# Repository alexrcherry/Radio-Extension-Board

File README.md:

# Radio-Extension-Board
KiCad PCB design files 

## Purpose
The purpose of this board is to transmit data to the ground station and also to determine altitude. Recovery on liquid rockets does not have a good track record so it is good to get max altitude data back to the ground without requiring the recovery to work. The radio chip used for this board also has the ability to do ranging. With multiple ground stations spaced apart, a primitive form of GPS can be used to determine the position and altitude of the rocket. This may be the primary form of altitude determination for the spaceshot since GPS cuts out at 80km. Accelerometer integration may be used in conjunction with or instead of the radio ranging. 

## Key ICs
STM32G4A1KEU6  
SX1280  
MCP2557FD

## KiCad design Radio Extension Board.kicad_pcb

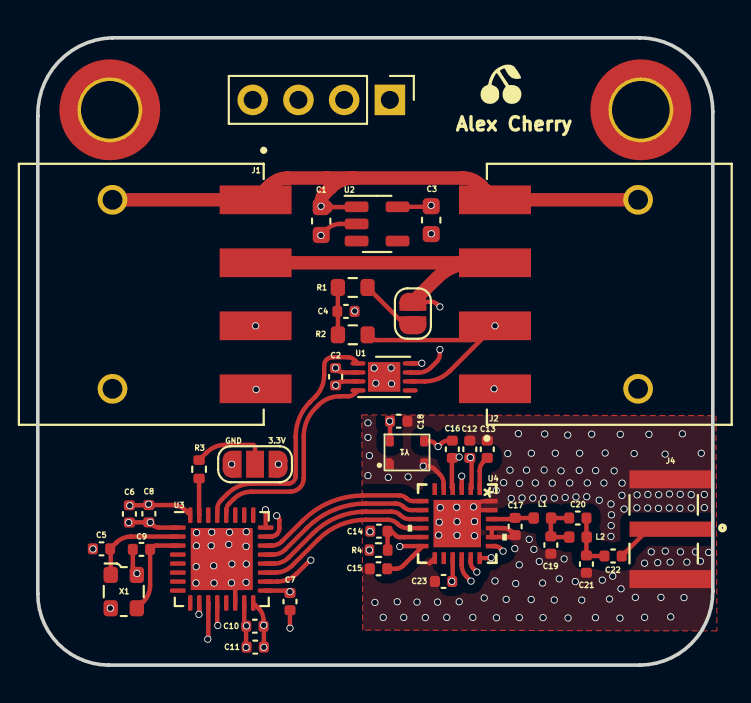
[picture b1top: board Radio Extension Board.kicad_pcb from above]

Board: 6 copper layers, 37.5 x 34.8 mm, 44 parts (0 on the bottom side), 32 nets.

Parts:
Alex Cherry : LOGO; Cherry
C1, C3: 1uF/10V/X7R; C_0603_1608Metric
C2: 0.1uF; C_0402_1005Metric
C4: 4.7nF; C_0402_1005Metric
C5, C9: 20pF; C_0402_1005Metric
C6, C7, C14, C23: 100nF; C_0402_1005Metric
C8: 4.7uF; C_0402_1005Metric
C10, C13, C18: 10nF; C_0402_1005Metric
C11: 1uF; C_0402_1005Metric
C12: 10nf; C_0402_1005Metric
C15: 470nF; C_0402_1005Metric
C16: 1nF; C_0402_1005Metric
C17: 0.8pF; C_0402_1005Metric
C19, C21: 1.2pF; C_0402_1005Metric
C20: 0.5pF; C_0402_1005Metric
C22: 100pF; C_0402_1005Metric
H1, H2: MountingHole; MountingHole_3.2mm_M3_DIN965_Pad_TopOnly
J1, J2: 1824543; PHOENIX_1824543
J3: Debug; PinHeader_1x04_P2.54mm_Vertical
J4: EMPCB.SMAFSTJ.B.HT; TAOGLAS_EMPCB.SMAFSTJ.B.HT
L1: 3.0nH; L_0402_1005Metric
L2: 2.5nH; L_0402_1005Metric
R1, R2: 60 ohm; R_0603_1608Metric
R3: 10k; R_0402_1005Metric
R4: 0R; R_0402_1005Metric
SW1: SW_SPST; SolderJumper-2_P1.3mm_Open_RoundedPad1.0x1.5mm
SW2: SW_SPDT; SolderJumper-3_P1.3mm_Open_RoundedPad1.0x1.5mm_NumberLabels
U1: MCP2557FD-xMNY; TDFN-8-1EP_3x2mm_P0.5mm_EP1.80x1.65mm
U2: MIC5504-3.3YM5; SOT-23-5
U3: STM32G4A1KEUx; QFN-32-1EP_5x5mm_P0.5mm_EP3.45x3.45mm
U4: SX1280IMLTRT; QFN24_4X4_SEM-L
X1: ECS-2520MV-xxx-xx; Oscillator_SMD_ECS_2520MV-xxx-xx-4Pin_2.5x2.0mm
Y1: TX0369B

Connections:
52Mhz XTAL: C16.1, U4.4 (XTA)
+3.3V: C2.1, C3.2, C6.1, C7.1, C8.1, C10.1, C11.1, C18.2, C23.1, J3.4, R4.1, SW2.3 (C), U1.3 (VDD), U2.5 (VOUT), U3.1 (VDD), U3.15 (VDDA), U3.17 (VDD), U4.15 (VBAT), Y1.4 (VCC)
+5V: C1.2, J1.1, J1.1_1 (1), J2.4, J2.4_1 (4), U2.1 (VIN), U2.3 (EN)
BOOT0: R3.1, U3.31 (PB8)
BUSY: U3.22 (PA12), U4.7 (BUSY)
CAN_H: J1.2, J2.3, SW1.2 (B), U1.7 (CANH)
CAN_L: J1.3, J2.2, R2.2, U1.6 (CANL)
CAN_RX: U1.4 (RXD), U3.28 (PB5)
CAN_TX: U1.1 (TXD), U3.29 (PB6)
CS_Radio: U3.18 (PA8), U4.19 (NSS_CTS)
DIO1: U3.21 (PA11), U4.8 (DIO1)
DIO2: U3.20 (PA10), U4.9 (DIO2)
DIO3: U3.19 (PA9), U4.10 (DIO3)
GND: C1.1, C2.2, C3.1, C4.2, C5.2, C6.2, C7.2, C8.2, C9.2, C10.2, C11.2, C12.2, C13.2, C14.2, C15.2, C17.2, C18.1, C19.2, C21.2, C23.2, J1.4, J1.4_1 (4), J2.1, J2.1_1 (1), J3.1, J4.SH1, J4.SH2, J4.SH3, J4.SH4, SW2.1 (A), U1.2 (VSS), U1.8 (S), U1.9 (VSS), U2.2 (GND), U3.14 (VSSA), U3.16 (VSS), U3.32 (VSS), U3.33 (VSS), U4.5 (GND), U4.13 (GND), U4.20 (GND), U4.21 (GND), U4.23 (GND), U4.24 (GND), U4.25 (GND), X1.2 (GND), X1.4 (VDD), Y1.1 (GND), Y1.2 (GND)
unnamed: C4.1, R1.2, R2.1
unnamed: C19.1, C20.1, L1.2, L2.1
unnamed: C20.2, C21.1, C22.1, L2.2
unnamed: C22.2, J4.1
unnamed: R1.1, SW1.1 (A)
unnamed: R3.2, SW2.2 (B)
unnamed: C12.1, C15.1, U4.2 (VDD_INN), U4.12 (DCC_FB)
unnamed: C14.1, R4.2, U4.11 (VBAT_IO)
unnamed: C13.1, U4.1 (VR_PA)
unnamed: C16.2, Y1.3 (OUTPUT)
RCC_OSC_IN: C5.1, U3.2 (PF0), X1.1 (Tri-State)
RCC_OSC_OUT: C9.1, U3.3 (PF1), X1.3 (OUT)
RFIO: C17.1, L1.1, U4.22 (RFIO)
SPI1_MISO: U3.11 (PA6), U4.16 (MISO_TX)
SPI1_MOSI: U3.12 (PA7), U4.17 (MOSI_RX)
SPI1_SCK: U3.10 (PA5), U4.18 (SCK_RTSN)
SYS_SWCLK: J3.2, U3.24 (PA14)
SYS_SWDIO: J3.3, U3.23 (PA13)

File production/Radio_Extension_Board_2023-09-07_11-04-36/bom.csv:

Designator,Footprint,Quantity,Value,LCSC Part #
"C1, C3",0603,2,1uF/10V/X7R,
"C10, C12, C13, C18",0402,4,10nF,
C11,0402,1,1uF,
"C14, C23, C6, C7",0402,4,100nF,
C15,0402,1,470nF,
C16,0402,1,1nF,
C17,0402,1,0.8pF,
"C19, C21",0402,2,1.2pF,
C2,0402,1,0.1uF,
C20,0402,1,0.5pF,
C22,0402,1,100pF,
C4,0402,1,4.7nF,
"C5, C9",0402,2,20pF,
C8,0402,1,4.7uF,
"H1, H2",MountingHole_3.2mm_M3_DIN965_Pad_TopOnly,2,MountingHole,
"J1, J2",PHOENIX_1824543,2,1824543,
J3,PinHeader_1x04_P2.54mm_Vertical,1,Debug,
J4,TAOGLAS_EMPCB.SMAFSTJ.B.HT,1,EMPCB.SMAFSTJ.B.HT,
L1,0402,1,3.0nH,
L2,0402,1,2.5nH,
"R1, R2",0603,2,60 ohm,
R3,0402,1,10k,
R4,0402,1,0R,
SW1,SolderJumper-2_P1.3mm_Open_RoundedPad1.0x1.5mm,1,SW_SPST,
SW2,SolderJumper-3_P1.3mm_Open_RoundedPad1.0x1.5mm_NumberLabels,1,SW_SPDT,
U1,TDFN-8-1EP_3x2mm_P0.5mm_EP1.80x1.65mm,1,MCP2557FD-xMNY,
U2,SOT-23-5,1,MIC5504-3.3YM5,
U3,QFN-32-1EP_5x5mm_P0.5mm_EP3.45x3.45mm,1,STM32G4A1KEUx,
U4,QFN24_4X4_SEM-L,1,SX1280IMLTRT,
X1,Oscillator_SMD_ECS_2520MV-xxx-xx-4Pin_2.5x2.0mm,1,ECS-2520MV-xxx-xx,
Y1,TX0369B,1,~,

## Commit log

2023-10-17 added files
